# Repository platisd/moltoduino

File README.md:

# Moltoduino
Add programmable cores to your project and enable Hardware In the Loop (HIL) testing.

## What?
Moltoduino is an Arduino shield that enables the stacking of multiple ATMega328P microcontrollers. The microcontroller pins are broken out in two ways:
* Outwards, to enable their arbitrary connection to different components or other pins via cables.
* Inwards, to enable their connection to the respective pin of the bottommost Arduino via jumpers.

The firmware on the Moltoduino cores can be easily flashed by flipping a switch that sets them in programming mode and then using the bottommost Arduino as an ISP programmer. You can read more about the project on [platis.solutions](https://platis.solutions/blog/2018/02/22/moltoduino-extra-cores-hil-testing/).

## Why?
Moltoduino is essentially a barebones Arduino UNO in the form of a shield that can be easily reprogrammed. So, what can you do with it?

* Parallelize time-consuming or time-critical functionality (e.g. reading sensor data, playing sound)
* Have a dedicated microcontroller for computationally intensive operations (e.g. Fast Fourier Transform)
* Enable Hardware In the Loop (HIL) testing
* Get additional resources, such as I/O pins, external interrupts, Serial port, I2C bus etc
* Save physical space needed for applications that require a more than one microcontrollers (e.g. by stacking them instead placing them next to each other)

## How?
Moltoduino was initially created with the purpose of providing a stackable pin extension solution for Arduino boards. During development, another use case emerged which involved the shield being used for HIL testing.

The picture below illustrates how the pins of the shield's ATMega328P are broken out, highlighting them with **green**. In **red** one can find the bottom Arduino's pins. It becomes apparent that pins that follow the Arduino numbering convention can be easily connected via jumpers (e.g. D1 with D1) regardless of which specific Arduino board is in place (i.e. Mega or Uno). Furthermore, the shield's pins are also broken on the sides of the board so to be accessible when multiple Moltoduinos or other shields are stacked on top.

### Pin extension
Attaching a Moltoduino shield is more or less equivalent to placing an Arduino Uno on top of another Uno or Mega board. The cool part is that it doesn't take up any horizontal real estate. You program them to perform an individual task in parallel or connect the Arduinos together via Serial, I2C or otherwise to implement complex functionality.

The pins facing outward can interface with the external components while the inward facilitate connection to the bottom Arduino, especially via I2C or Serial.

### HIL testing
Moltoduino can be utilized to provide a _hobby-grade_ [HIL testing](http://www.hil-simulation.com/home/hil-testing.html) solution for your embedded project. Having two microcontrollers that are easily connected to each other it is possible to conduct HIL simulations. This is achieved by one microcontroller running the production code and the other running the HIL test which generates input for the system under test and reads its output.

Such a HIL test fixture allows you to automate system-level testing on your project by mimicking real-world input. This can be a difficult and laborious process, where the tester would have to manually provide the environment input and check the output so to verify the system. Check out the relevant [code examples](#code-examples) to see how a HIL implementation could look like.

### Programming Moltoduino
1. Have all switches (there is one on each Moltoduino), in the "operation" position instead of "programming" mode
2. In the Arduino IDE, upload the ArduinoISP sketch to the "bottom" Arduino
3. Open the sketch to upload to the Nth Moltoduino on the Arduino IDE
4. Make sure that "Arduino as ISP" is chosen under Tools :arrow_right: Programmer
5. Choose the Arduino Uno as the target board, under Tools :arrow_right: Board :arrow_right: Arduino/Genuino UNO
6. Put the switch in the "programming" position, on the Moltoduino(s) you wish to program
7. (If not previously done) Burn the bootloader, under Tools :arrow_right: Burn bootloader
8. Upload sketch using programmer, under Sketch :arrow_right: Upload sketch using programmer
9. Put the switch back in the "operation" position, otherwise uploading to the bottom Arduino will not be possible

## Code examples
For the code examples the [Smartcar shield](http://plat.is/smartcar) library will be used. You can easily download it via your Arduino IDE library manager.

### Controlling a Smartcar via UART
In this scenario, a [Smartcar](http://plat.is/smartcar) is being controlled via UART (e.g. an HC-06 Bluetooth dongle) and we want to verify its behavior. The HIL simulation will be running on an Arduino Mega while the system under test firmware will be uploaded onto a Moltoduino that is stacked on top.

**System under test**

The following code should be straight forward. Depending on the UART input the Smartcar should change speed and direction. We are steering the Smartcar with a servo motor while the speed is controlled by a brushed motor. We will be sending commands via UART and reading the PWM steering signal as well as the brushed motor control signals in order to verify the Smartcar's intended behavior.

```cpp
#include <Smartcar.h>

const int SERVO_PIN = 3;
const int FORWARD_PIN = 8;
const int BACKWARD_PIN = 7;
const int THROTTLE_PIN = 6;
const int fSpeed = 70; // 70% of the full speed forward
const int bSpeed = -70; // 70% of the full speed backward
const int lDegrees = -50; // Degrees to turn left
const int rDegrees = 50; // Degrees to turn right

// Initialize the car, that uses a servo motor for steering
// and a brushed DC motor to pins 8,7 (direction) and 6 (PWM) for throttling
Car car(useServo(SERVO_PIN), useDCMotor(FORWARD_PIN, BACKWARD_PIN, THROTTLE_PIN));

void setup() {
  Serial.begin(9600);
  car.begin(); // Initialize the car using the encoders and the gyro
}

void loop() {
  handleInput();
}

void handleInput() { // Handle serial input if there is any
  if (Serial.available()) {
    char input = Serial.read();
    switch (input) {
      case 'l': // Turn counter-clockwise going forward
        car.setSpeed(fSpeed);
        car.setAngle(lDegrees);
        break;
      case 'r': // Turn clock-wise
        car.setSpeed(fSpeed);
        car.setAngle(rDegrees);
        break;
      case 'f': // Go ahead
        car.setSpeed(fSpeed);
        car.setAngle(0);
        break;
      case 'b': // Go back
        car.setSpeed(bSpeed);
        car.setAngle(0);
        break;
      default: // If you receive something that you don't know, just stop
        car.setSpeed(0);
        car.setAngle(0);
    }
  }
}
```

**HIL simulation**

In this HIL test we need to simulate the input to the system (i.e. UART commands) and then observe its output (i.e. pin states and PWM signal) to verify production code's correct behavior. Moreover, jumpers are used to enable interaction between the system under test and the HIL simulation. The jumper placement is illustrated in the table below.

| HIL simulation | System Under Test | Purpose                           |
| :----:         |:----:             |:----:                             |
| TX             |  RX               | Transmit UART commands to the SUT |
| 3              |  3                | Read servo motor's PWM signal     |
| 7              |  7                | Read motor control pin            |
| 8              |  8                | Read motor control pin            |

```cpp
// Simulation pin configuration
const int STEERING_PIN = 3;
const int FORWARD_PIN = 8; // Car goes forward when set HIGH
const int BACKWARD_PIN = 7; // Car goes backward when set HIGH
const int THROTTLE_PIN = 6;
// UART commands
const char CAR_FORWARD = 'f';
const char CAR_BACKWARD = 'b';
const char CAR_LEFT = 'l';
const char CAR_RIGHT = 'r';
const char CAR_STOP = 's';
// Expected steering degrees
const int LEFT = -50;
const int RIGHT = 50;
const int STRAIGHT = 0;
// Other variables and structures
enum Throttle {
  FORWARD,
  BACKWARD,
  STOPPED,
};

bool isThrottle(Throttle expectedThrottle) {
  Throttle actualThrottle = STOPPED;
  if (digitalRead(FORWARD_PIN) && !digitalRead(BACKWARD_PIN)) {
    actualThrottle = FORWARD;
  } else if (!digitalRead(FORWARD_PIN) && digitalRead(BACKWARD_PIN)) {
    actualThrottle = BACKWARD;
  }

  return actualThrottle == expectedThrottle;
}

bool isSteering(int expectedAngle) {
  int pwm = pulseIn(STEERING_PIN, HIGH);
  // Map the PWM signal to a 0 to 180 scale
  const int MIN_PWM = 540;
  const int MAX_PWM = 2390;
  int measuredAngle = map(pwm, MIN_PWM, MAX_PWM, 0, 180);
  // Offset the angle by 90 to get an angle between -90 and 90
  measuredAngle -= 90;
  int absoluteDelta = expectedAngle > measuredAngle ?
                      expectedAngle - measuredAngle : measuredAngle - expectedAngle;
  // We are expecting some error in these measurements so let's define an acceptable error margin
  const int ERROR_MARGIN = 5;

  return absoluteDelta < ERROR_MARGIN;
}

void runSmartcarHIL(const char* testName, const char command, Throttle throttle, const int steering) {
  Serial.print("RUNNING: ");
  Serial.println(testName);
  // Send command
  Serial.print("Sending command: ");
  Serial.print(command);
  Serial.flush(); // Make sure we have finished sending
  // Wait a bit to make sure the command has been processed
  const unsigned long TEST_DELAY = 100;
  delay(TEST_DELAY);
  String result = isThrottle(throttle) && isSteering(steering) ? "PASSED" : "FAILED";
  Serial.print("\nRESULT: ");
  Serial.println(result);
  Serial.println("----");
}

void goForward_test() {
  auto UARTcommand = CAR_FORWARD;
  auto expectedThrottle = FORWARD;
  auto expectedSteering = STRAIGHT;
  runSmartcarHIL(__func__, UARTcommand, expectedThrottle, expectedSteering);
}

void goBackward_test() {
  auto UARTcommand = CAR_BACKWARD;
  auto expectedThrottle = BACKWARD;
  auto expectedSteering = STRAIGHT;
  runSmartcarHIL(__func__, UARTcommand, expectedThrottle, expectedSteering);
}

void turnLeft_test() {
  auto UARTcommand = CAR_LEFT;
  auto expectedThrottle = FORWARD;
  auto expectedSteering = LEFT;
  runSmartcarHIL(__func__, UARTcommand, expectedThrottle, expectedSteering);
}

void turnRight_test() {
  auto UARTcommand = CAR_RIGHT;
  auto expectedThrottle = FORWARD;
  auto expectedSteering = RIGHT;
  runSmartcarHIL(__func__, UARTcommand, expectedThrottle, expectedSteering);
}

void stop_test() {
  auto UARTcommand = CAR_STOP;
  auto expectedThrottle = STOPPED;
  auto expectedSteering = STRAIGHT;
  runSmartcarHIL(__func__, UARTcommand, expectedThrottle, expectedSteering);
}

void setup() {
  pinMode(FORWARD_PIN, INPUT);
  pinMode(BACKWARD_PIN, INPUT);
  pinMode(STEERING_PIN, INPUT);
  Serial.begin(9600);
  Serial.println("====================");
  Serial.println("Starting HIL test suite");
  Serial.println("====================");

  goForward_test();
  goBackward_test();
  turnLeft_test();
  turnRight_test();
  stop_test();
}

void loop() {
}
```

### Controlling a light based on ultrasound sensor distance measurements
In this scenario, an `HC-SR04` ultrasound sensor is being used to measure distances. When an object is detected close enough a light turns on. Yet again, the HIL simulation will be running on an Arduino Mega while the system under test firmware will be uploaded onto a Moltoduino that is stacked on top.

**System under test**

Below you can find a simplified implementation of the typical use case in which a light needs to be turned on when an object is detected at a nearby distance otherwise it should be off. The `HC-SR04` class of [Smartcar shield](http://plat.is/smartcar) library is utilized to conduct the measurements.

```cpp
#include <Smartcar.h>

SR04 sensor;
const int TRIGGER_PIN = 2;
const int ECHO_PIN = 3;
const int LIGHT_PIN = 9;
const int MIN_OBSTACLE_DISTANCE = 15; // In centimeters

void setup() {
  sensor.attach(TRIGGER_PIN, ECHO_PIN);
  pinMode(LIGHT_PIN, OUTPUT);
}

void loop() {
  auto distance = sensor.getDistance();
  // If there is an obstacle nearby turn the light on
  if (distance > 0 && distance < MIN_OBSTACLE_DISTANCE) {
    digitalWrite(LIGHT_PIN, HIGH);
  } else {
    digitalWrite(LIGHT_PIN, LOW);
  }
  delay(100);
}
```

**HIL simulation**

In this HIL test we need to simulate the `HC-SR04` ultrasound sensor's input to the system and then observe its output (i.e. the pin that controls the state of the light). Particularly, we observe (via an interrupt) the incoming signals from the trigger pin of the system under test, an event which designates that a measurement has been initiated. Next, we simulate the sensor input by calculating and producing a pulse of equal length to the one that would have been generated, should there have been an actual sensor and an object. Finally, we verify the digital pin that controls the light is in the appropriate state.

Jumpers are used to enable interaction between the system under test and the HIL simulation. The jumper placement is illustrated in the table below.

| HIL simulation | System Under Test | Purpose              |
| :----:         |:----:             |:----:                |
| 2              |  2                | Read trigger signal  |
| 3              |  3                | Generate echo pulse  |
| 9              |  9                | Read light pin state |

```cpp
const int TRIGGER_PIN = 2;
const int ECHO_PIN = 3;
const int LIGHT_PIN = 9;

volatile unsigned long echoDuration = 0;

void generateEcho() {
  if (echoDuration == 0) {
    // If no echo duration has been set or set to 0
    // then return immediately as no pulse is to be generated
    return;
  }
  digitalWrite(ECHO_PIN, LOW); // Set LOW first for cleaner signal
  delayMicroseconds(3);
  // Simulate the echo pulse of an HC-SR04 sensor
  digitalWrite(ECHO_PIN, HIGH);
  delayMicroseconds(echoDuration);
  digitalWrite(ECHO_PIN, LOW);
}

/**
   Accordig to the HC-SR04 datasheet (https://goo.gl/b22dp3) the formula to
   determine the distance in centimeters is: cm = uSec / 58
   We need to calculate the length of the pulse in microseconds
   that we has to be generated to simulate a specific distance in cm.
*/
void setEchoPulseDurationFor(unsigned int cm) {
  noInterrupts();
  echoDuration = cm * 58;
  interrupts();
}

void runUltrasoundHIL(const char* testName, int obstacleDistance, int expectedLEDState) {
  Serial.print("RUNNING: ");
  Serial.println(testName);
  setEchoPulseDurationFor(obstacleDistance);
  const unsigned long TEST_DELAY = 300;
  delay(TEST_DELAY); // Wait a bit for a new measurement to start
  String result = digitalRead(LIGHT_PIN) == expectedLEDState ? "PASSED" : "FAILED";
  Serial.print("\nRESULT: ");
  Serial.println(result);
  Serial.println("----");
}

void whenObstacleNear_lightTurnsOn_test() {
  auto obstacleDistance = 10;
  auto expectedLEDState = HIGH;
  runUltrasoundHIL(__func__, obstacleDistance, expectedLEDState);
}

void whenObstacleFar_lightTurnsOff_test() {
  auto obstacleDistance = 15;
  auto expectedLEDState = LOW;
  runUltrasoundHIL(__func__, obstacleDistance, expectedLEDState);
}

void whenNoObstacle_lightTurnsOff_test() {
  auto obstacleDistance = 0;
  auto expectedLEDState = LOW;
  runUltrasoundHIL(__func__, obstacleDistance, expectedLEDState);
}

void setup() {
  pinMode(LIGHT_PIN, INPUT);
  pinMode(TRIGGER_PIN, INPUT);
  pinMode(ECHO_PIN, OUTPUT);
  // Setup interrupt for trigger pin which goes HIGH when a measurement begins
  attachInterrupt(digitalPinToInterrupt(TRIGGER_PIN), generateEcho, FALLING);
  Serial.begin(9600);
  Serial.println("====================");
  Serial.println("Starting HIL test suite");
  Serial.println("====================");

  whenObstacleNear_lightTurnsOn_test();
  whenObstacleFar_lightTurnsOff_test();
  whenNoObstacle_lightTurnsOff_test();
}

void loop() {
}
```

## Bill Of Materials
| Quantity | Value            | Device                                    | Package                   |
|----------|----------------- |-------------------------------------------|---------------------------|
| 1        | Moltoduino PCB   | ARDUINO_R3_ICSP                           | ARDUINOR3_ICSP            |
| 1        | ATMEGA328P_PDIP  | ATMEGA328P_PDIP                           | DIL28-3                   |
| 1        | BC547            | TRANSISTOR_NPNBC547                       | TO-92-AMMO                |
| 3        | 100nf            | DIP-CERAMIC-DISC-100NF-50V-Y5V(D5.0MM)    | CERAMIC-2.54              |
| 1        | 150Ω             | DIP-RES-1K-5%-1/4W(PR-D2.3XL6.5MM)        | PR-D2.3XL6.5MM            |
| 1        | 16MHZ            | DIP-CRYSTAL-16MHZ-18PF-30PPM-50R(HC49US)  | HC49US                    |
| 1        | 1K               | DIP-RES-1K-5%-1/4W(PR-D2.3XL6.5MM)        | PR-D2.3XL6.5MM            |
| 2        | 22pf             | DIP-CERAMIC-DISC-22PF-50V-10%-NPO(D4.0MM) | CERAMIC-2.54              |
| 1        | 2x16p-2.54       | DIP-BLACK-MALE-HEADER-VERT(2X16P-2.54)    | H2X16-2.54                |
| 1        | 2x6p-2.54        | DIP-BLACK-MALE-HEADER(2X6P-2.54)          | H2X6-2.54                 |
| 2        | 4.7K             | DIP-RES-4.7K-5%-1/4W(PR-D2.3XL6.5MM)      | PR-D2.3XL6.5MM            |
| 4        | 7p-2.54-90d      | DIP-BLACK-MALE-HEADER(7P-2.54-90D)        | H7-2.54-90D-MALE          |
| 1        | AD595AQ-DIP14    | 74HC4066(DIP14)                           | DIP14-2.54-17.24X6.35MM   |
| 1        | SK-12D01         | DIP-TOGGLE-SWITCH-ON-ON(3+2P-8.8X4.6MM)   | SW5-2.0-8.8X4.4X4.7MM-90D |
| 1        | SR302DC          | DIP-LED-RED-RED(2P-D3MM)                  | LED2-2.54-D3.0MM          |
| 1        | TS-1101F         | DIP-BUTTON-FRONT-WHITE(2P-3.4X6MM)        | SW2-3.4X6.0X3.55MM-90D    |

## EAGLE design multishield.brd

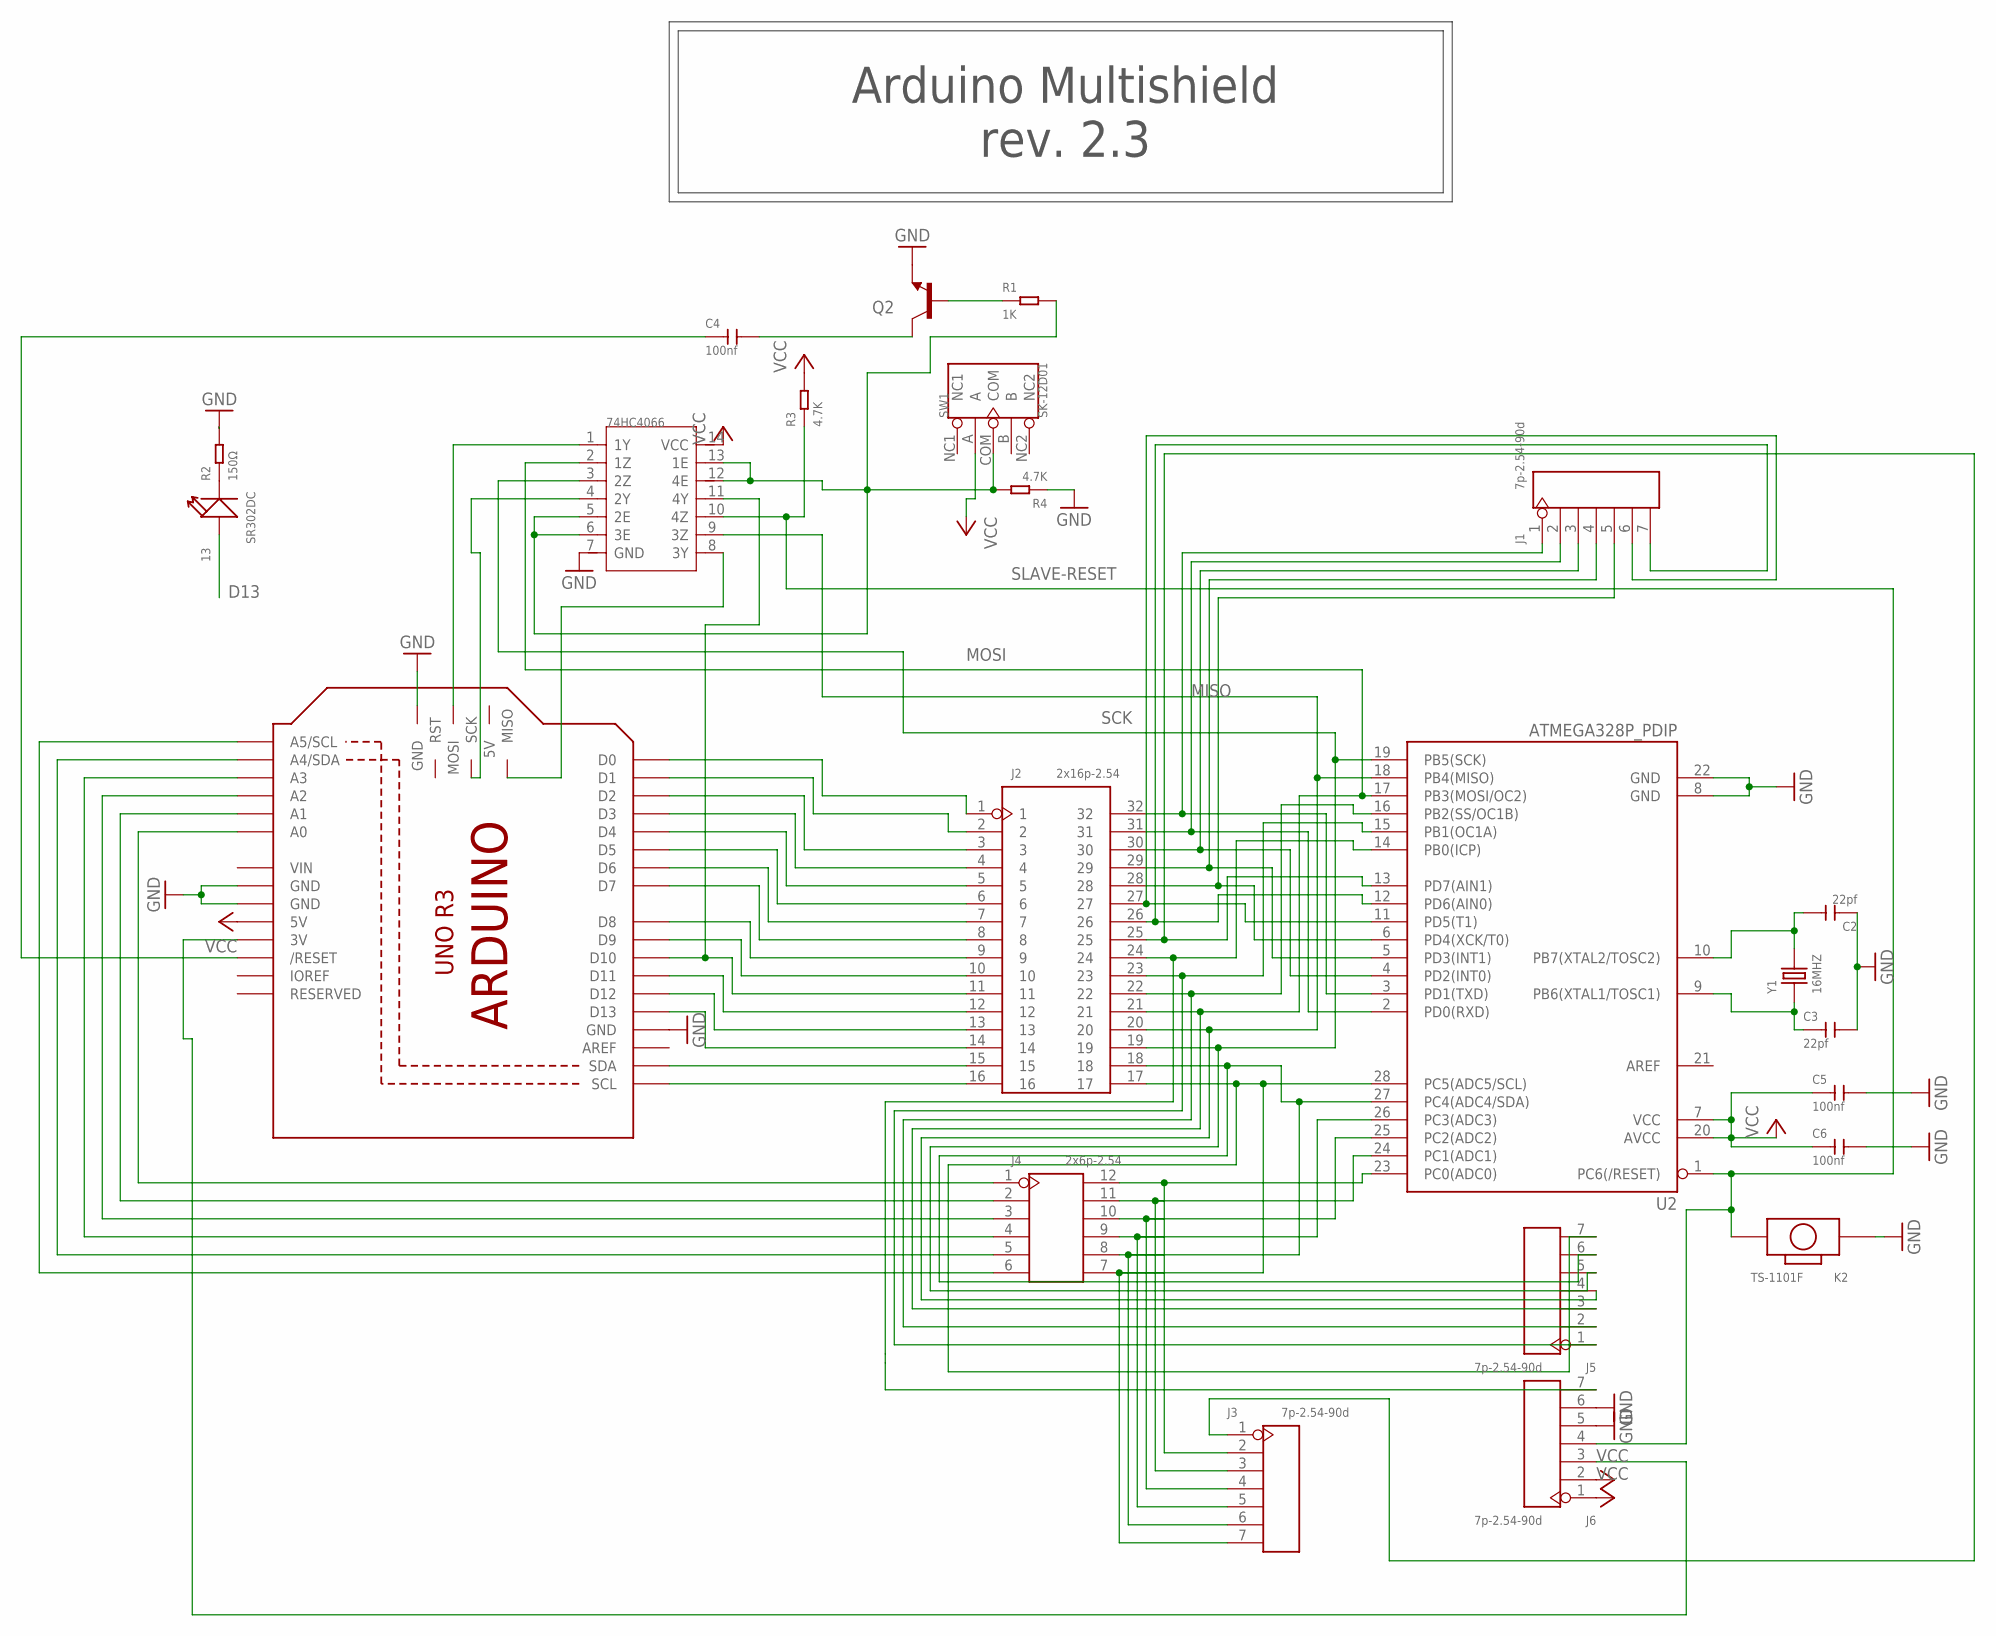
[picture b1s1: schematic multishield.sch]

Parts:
13: SR302DC; LED2-2.54-D3.0MM
C2, C3: 22pf; CERAMIC-2.54
C4, C5, C6: 100nf; CERAMIC-2.54
J1, J3, J5, J6: 7p-2.54-90d; H7-2.54-90D-MALE
J2: 2x16p-2.54; H2X16-2.54
J4: 2x6p-2.54; H2X6-2.54
K2: TS-1101F; SW2-3.4X6.0X3.55MM-90D
M1: ARDUINO_R3_ICSP; ARDUINOR3_ICSP
Q2: TRANSISTOR_NPNBC547; TO-92-AMMO
R1: 1K; PR-D2.3XL6.5MM
R2: 150Ω; PR-D2.3XL6.5MM
R3, R4: 4.7K; PR-D2.3XL6.5MM
SW1: SK-12D01; SW5-2.0-8.8X4.4X4.7MM-90D
U1: AD595AQ-DIP14; DIP14-2.54-17.24X6.35MM
U2: ATMEGA328P_PDIP; DIL28-3
Y1: 16MHZ; HC49US

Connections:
D9A: J2.10, M1.D9
D9B: J2.23, J5.1, U2.15 (PB1(OC1A))
GND: C2.1, C3.2, C5.2, C6.2, J6.5, J6.6, K2.P$1 (1), M1.GND, M1.GND@1 (GND), M1.GND@2 (GND), M1.GND@3 (GND), Q2.3 (E), R2.2, R4.1, U1.7 (GND), U2.8 (GND), U2.22 (GND)
MISO: J2.20, J5.4, U1.9 (3Z), U2.18 (PB4(MISO))
MOSI: J2.21, J5.3, U1.2 (1Z), U2.17 (PB3(MOSI/OC2))
unnamed: J2.1, M1.D0
unnamed: J2.2, M1.D1
unnamed: J2.3, M1.D2
unnamed: J2.4, M1.D3
unnamed: J2.5, M1.D4
unnamed: J2.6, M1.D5
unnamed: J2.7, M1.D6
unnamed: J2.8, M1.D7
unnamed: J2.9, M1.D8
unnamed: 13.K (-), R2.1
unnamed: J2.11, M1.D10, U1.11 (4Y)
unnamed: J2.12, M1.D11
unnamed: J2.13, M1.D12
unnamed: J2.14, M1.D13
unnamed: J2.15, M1.SDA
unnamed: J2.16, M1.SCL
unnamed: J1.1, J2.32, U2.3 (PD1(TXD))
unnamed: J1.2, J2.31, U2.2 (PD0(RXD))
unnamed: J1.3, J2.30, U2.4 (PD2(INT0))
unnamed: J1.4, J2.29, U2.5 (PD3(INT1))
unnamed: J1.5, J2.28, U2.6 (PD4(XCK/T0))
unnamed: J1.6, J2.27, U2.11 (PD5(T1))
unnamed: J4.1, M1.A0
unnamed: J2.25, J3.1, U2.13 (PD7(AIN1))
unnamed: J2.24, J6.7, U2.14 (PB0(ICP))
unnamed: J2.22, J5.2, U2.16 (PB2(SS/OC1B))
unnamed: C4.2, Q2.1 (C)
unnamed: C4.1, M1.RESET (/RESET)
unnamed: Q2.2 (B), R1.1
unnamed: M1.MOSI, U1.1 (1Y)
unnamed: M1.SCK, U1.4 (2Y)
unnamed: J1.7, J2.26, U2.12 (PD6(AIN0))
unnamed: J4.2, M1.A1
unnamed: J4.3, M1.A2
unnamed: J4.4, M1.A3
unnamed: J3.2, J4.12, U2.23 (PC0(ADC0))
unnamed: J3.3, J4.11, U2.24 (PC1(ADC1))
unnamed: J3.4, J4.10, U2.25 (PC2(ADC2))
unnamed: J3.5, J4.9, U2.26 (PC3(ADC3))
unnamed: J2.18, J3.6, J4.8, J5.6, U2.27 (PC4(ADC4/SDA))
unnamed: J2.17, J3.7, J4.7, J5.7, U2.28 (PC5(ADC5/SCL))
unnamed: J4.5, M1.A4 (A4/SDA)
unnamed: J4.6, M1.A5 (A5/SCL)
unnamed: M1.MISO, U1.8 (3Y)
unnamed: J6.3, M1.3V
unnamed: C2.2, U2.10 (PB7(XTAL2/TOSC2)), Y1.2
unnamed: R1.2, R4.2, SW1.COM, U1.5 (2E), U1.6 (3E), U1.12 (4E), U1.13 (1E)
unnamed: C3.1, U2.9 (PB6(XTAL1/TOSC1)), Y1.1
SCK: 13.A (+), J2.19, J5.5, U1.3 (2Z), U2.19 (PB5(SCK))
SLAVE-RESET: J6.4, K2.P$2 (2), R3.1, U1.10 (4Z), U2.1 (PC6(/RESET))
VCC: C5.1, C6.1, J6.1, J6.2, M1.5V, R3.2, SW1.A, U1.14 (VCC), U2.7 (VCC), U2.20 (AVCC)
VIN: M1.VIN

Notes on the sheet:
Arduino Multishield rev. 2.3
D13

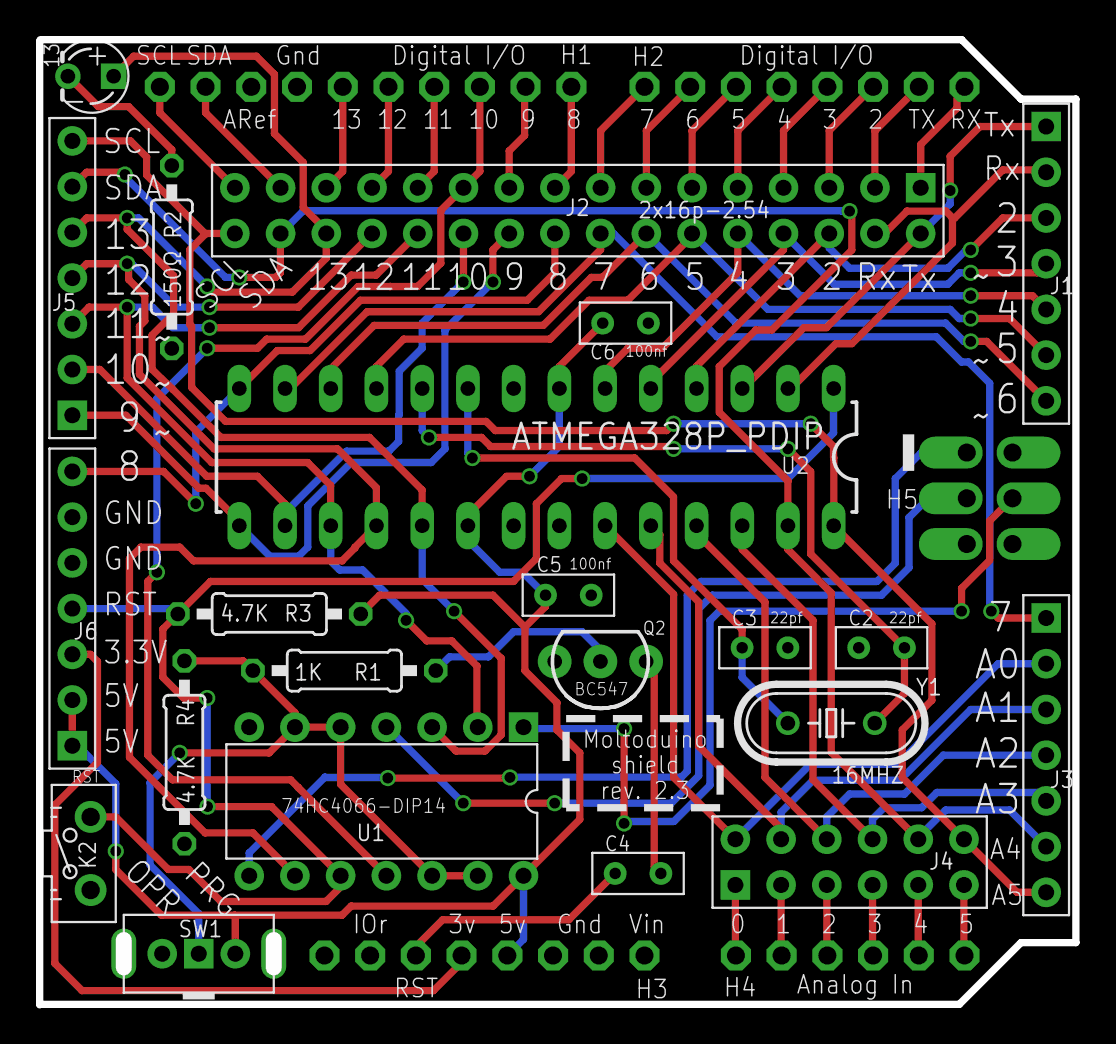
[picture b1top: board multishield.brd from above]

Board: 2 copper layers, 57.6 x 53.6 mm, 24 parts (0 on the bottom side), 56 nets.

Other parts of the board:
U$4: OSHWLOGO_BACK_0.2

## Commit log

2016-02-24 adding gitignore
2016-02-24 updating gitignore
2016-02-24 initial upload
2016-02-25 adding shield with breakouts
2016-02-26 added most of the things by now, minor aesthetic additions left for rev.0
2016-02-26 various improvements + clock
2016-02-26 part replacements and bom
2016-03-02 rev. 0, BOM with prices
2016-03-28 adding 100nF capacitors and minor other changes
2016-03-30 rev 1
2016-04-06 latest updates
2016-04-06 7pin angled headers instead
2016-04-06 moved atmega328 to the left, to make more space for the isp header soldering
2016-04-06 moved atmega328 further to the left
2016-04-20 7-pin headers moved to the edges, some wiring refactored
2016-04-22 reset pin added, various changes (in pin packages to make soldering easier
2016-04-28 various improvements and addition of LED at D9
2016-04-29 changed 0 and 1 labels to rx and tx
2016-05-01 no more short circuiting while switch in the middle position
2016-06-08 version 2.2 (Led on D13)
2018-02-16 Small changes for rev. 2.3
2018-02-18 Add initial documentation
2018-02-21 Add BOM
2018-02-21 Update README
    * Add section
    * Add Smartcar control via UART code example
2018-02-21 Refactor BOM
    * Remove SKUs
    * Move Moltoduino shield and atmega328p chip to the top
2018-02-21 Remove BOM in gnumeric format
2018-02-21 Add ultrasound sensor distance HIL test example
2018-02-21 Change license to Apache
2018-02-22 Update README
    * Move link of code examples
    * Wording fix
2018-02-22 Change test signatures
    Let's keep it simple and not return anything
2018-02-22 Add short information about HIL testing
2018-02-22 Update images
    * Rotate pinout image
    * Cropped stacked moltoduinos photo
2018-02-22 Add link to blog artice
2018-02-22 Fix BOM entries
2018-02-22 Update BOM
2018-02-23 Add min and max PWM frequency variables
2018-03-07 Emphasize the Arduino IDE options

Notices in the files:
parts and their libraries:
SparkFun-DigitalIC: Licensing: Creative Commons ShareAlike 4.0 International - https://creativecommons.org/licenses/by-sa/4.0
